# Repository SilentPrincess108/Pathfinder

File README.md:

# Pathfinder
A hardware starter project made for Hack Club's Stasis! My version of the project allows you to play a memory-reaction game using led's and key buttons.

How it works:
- led's will light up in a random sequence
- the user than has to click the corresponding keys in order of the sequence within 5 seconds
- if the inputted sequence is correct, they gain a point, otherwise, they lose a life
- this goes on until the player loses all their lives

BOM:

|Item|Part Name       |Quantity|Description|Cost |Link                                                                                                                                                                                                                                                                                                                                                                                                                                                                                                                                                                                                                                                                                             |
|----|----------------|--------|-----------|-----|-------------------------------------------------------------------------------------------------------------------------------------------------------------------------------------------------------------------------------------------------------------------------------------------------------------------------------------------------------------------------------------------------------------------------------------------------------------------------------------------------------------------------------------------------------------------------------------------------------------------------------------------------------------------------------------------------|
|1   |LED             |10      |Light      |$1.17|https://www.aliexpress.com/item/32759416007.html?spm=a2g0o.productlist.main.25.5ad45d4fBpD18Y&algo_pvid=c7d3ffdf-054c-4a00-8b1f-7dc1258b8f89&algo_exp_id=c7d3ffdf-054c-4a00-8b1f-7dc1258b8f89-24&pdp_ext_f=%7B%22order%22%3A%2263%22%2C%22spu_best_type%22%3A%22price%22%2C%22eval%22%3A%221%22%2C%22fromPage%22%3A%22search%22%7D&pdp_npi=6%40dis%21CAD%212.47%211.60%21%21%211.76%211.14%21%402103110517740490152535062ebe05%2112000027866463708%21sea%21CA%217451194651%21ABX%211%210%21n_tag%3A-29910%3Bd%3A8fd05d1b%3Bm03_new_user%3A-29895%3BpisId%3A5000000197831969&curPageLogUid=rJeiEFxpdOuU&utparam-url=scene%3Asearch%7Cquery_from%3A%7Cx_object_id%3A32759416007%7C_p_origin_prod%3A|
|2   |Resistor        |100     |Resistor   |$0.73|https://www.aliexpress.com/item/1005006040209297.html?spm=a2g0o.productlist.main.1.44fe7785qfn6Bm&algo_pvid=6d8afb23-2538-424a-ae4a-d31f3bcf2f64&algo_exp_id=6d8afb23-2538-424a-ae4a-d31f3bcf2f64-0&pdp_ext_f=%7B%22order%22%3A%22341%22%2C%22spu_best_type%22%3A%22price%22%2C%22eval%22%3A%221%22%2C%22fromPage%22%3A%22search%22%7D&pdp_npi=6%40dis%21CAD%210.72%210.72%21%21%210.51%210.51%21%402101e80317740488821005309e1bc6%2112000035442807620%21sea%21CA%217451194651%21ABX%211%210%21n_tag%3A-29910%3Bd%3A8fd05d1b%3Bm03_new_user%3A-29895&curPageLogUid=NUwI7MvNd3uo&utparam-url=scene%3Asearch%7Cquery_from%3A%7Cx_object_id%3A1005006040209297%7C_p_origin_prod%3A                  |
|3   |Xiao rp 2040    |1       |PCB        |$3.59|https://www.aliexpress.com/item/1005003908237026.html?spm=a2g0o.cart.0.0.6df938dabXCDew&mp=1&pdp_npi=6%40dis%21CAD%21CAD%2011.73%21CAD%204.93%21%21CAD%204.75%21%21%21%40210328df17740487064442830e3672%2112000056511616306%21ct%21CA%217451194651%21%216%210%21                                                                                                                                                                                                                                                                                                                                                                                                                                 |
|4   |Cherry mx switch|10      |Input      |$2.60|https://www.aliexpress.com/item/1005008811335051.html?spm=a2g0o.cart.0.0.6df938dabXCDew&mp=1&pdp_npi=6%40dis%21CAD%21CAD%2052.73%21CAD%2045.79%21%21CAD%2044.15%21%21%21%40210328df17740487064442830e3672%2112000046764301536%21ct%21CA%217451194651%21%211%210%21                                                                                                                                                                                                                                                                                                                                                                                                                               |
|5   |PCB |5      |Board to connect all components for my pathfinder.     |$5.80            |https://jlcpcb.com/|JLCPCB     |

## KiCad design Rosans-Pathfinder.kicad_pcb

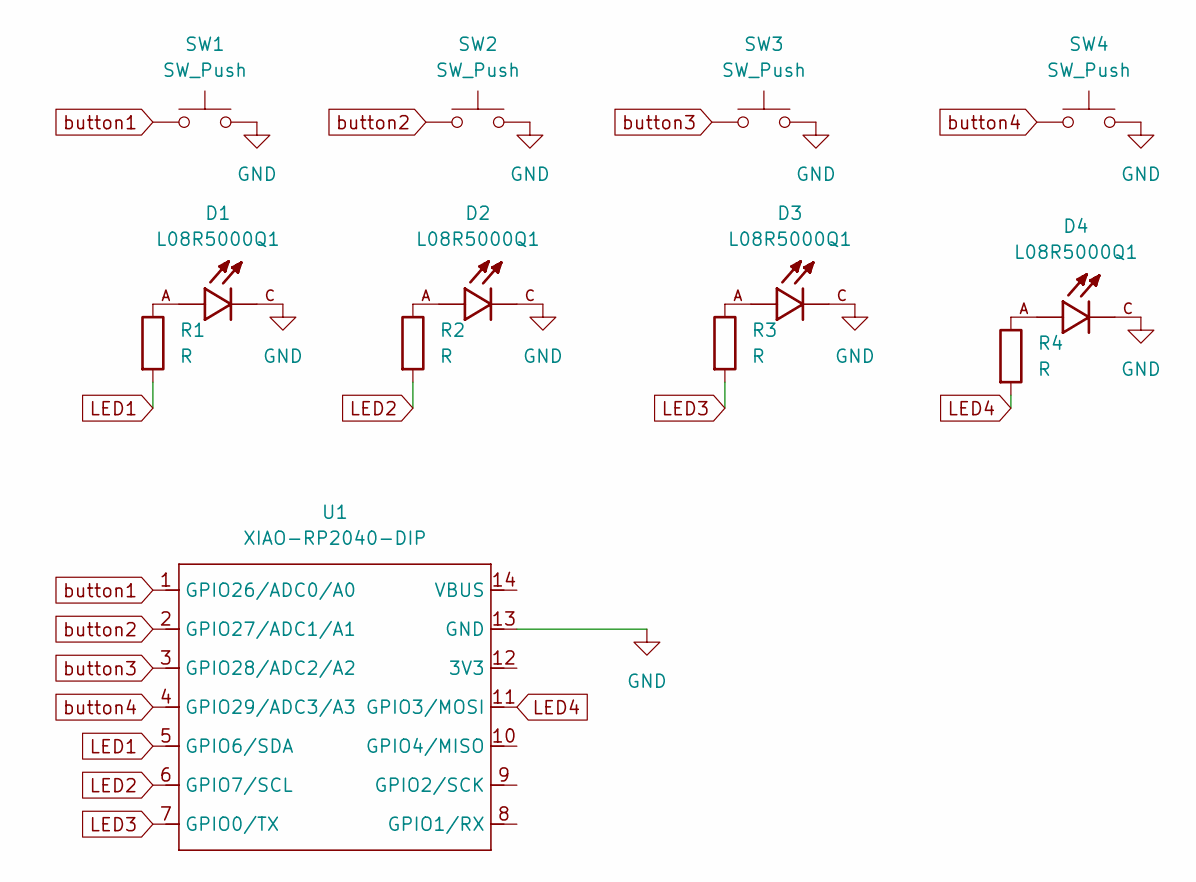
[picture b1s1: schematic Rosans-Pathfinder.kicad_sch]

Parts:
D1, D2, D3, D4: L08R5000Q1; LEDRD254W57D500H1070; PARTREV NA
R1, R2, R3, R4: R; R_Axial_DIN0204_L3.6mm_D1.6mm_P5.08mm_Horizontal
SW1, SW2, SW3, SW4: SW_Push; SW_Cherry_MX_1.00u_PCB
U1: XIAO-RP2040-DIP

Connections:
GND: D1.C, D2.C, D3.C, D4.C, SW1.2, SW2.2, SW3.2, SW4.2, U1.13 (GND)
LED1: R1.2, U1.5 (GPIO6/SDA)
LED2: R2.2, U1.6 (GPIO7/SCL)
LED3: R3.2, U1.7 (GPIO0/TX)
LED4: R4.2, U1.11 (GPIO3/MOSI)
unnamed: D1.A, R1.1
unnamed: D2.A, R2.1
unnamed: D3.A, R3.1
unnamed: D4.A, R4.1
button1: SW1.1, U1.1 (GPIO26/ADC0/A0)
button2: SW2.1, U1.2 (GPIO27/ADC1/A1)
button3: SW3.1, U1.3 (GPIO28/ADC2/A2)
button4: SW4.1, U1.4 (GPIO29/ADC3/A3)

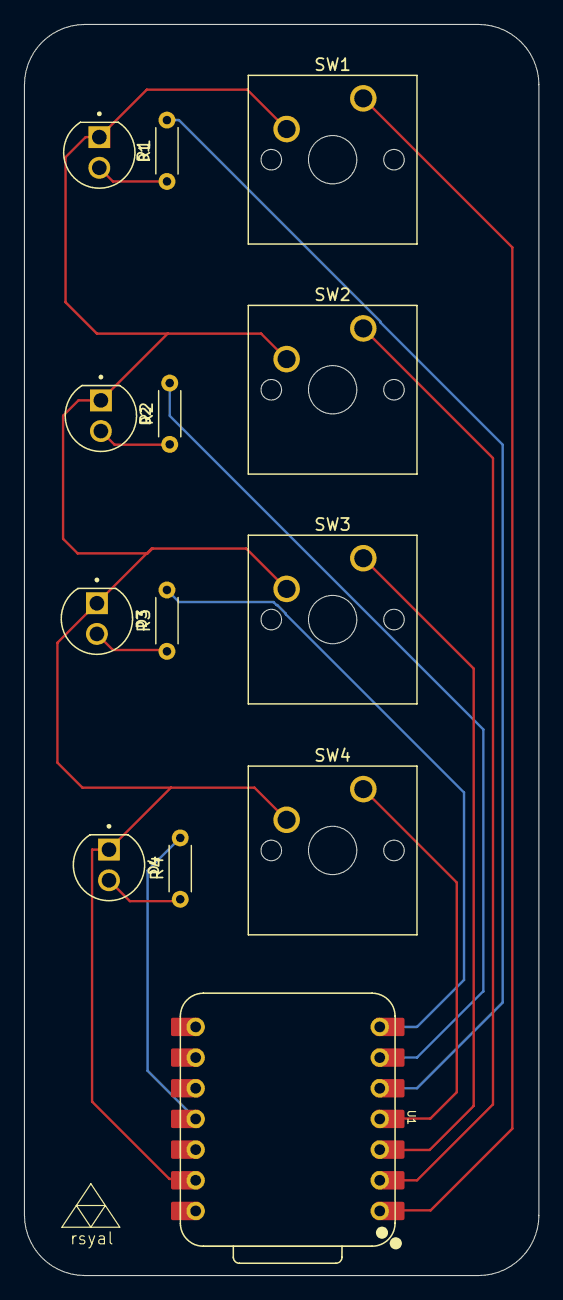
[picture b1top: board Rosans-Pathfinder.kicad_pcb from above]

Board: 2 copper layers, 42.6 x 103.6 mm, 13 parts (0 on the bottom side), 13 nets.

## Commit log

2026-04-05 all files for my pathfinder
2026-04-06 Fix price formatting for PCB entry in README
2026-04-06 Fix formatting of PCB entry in README
